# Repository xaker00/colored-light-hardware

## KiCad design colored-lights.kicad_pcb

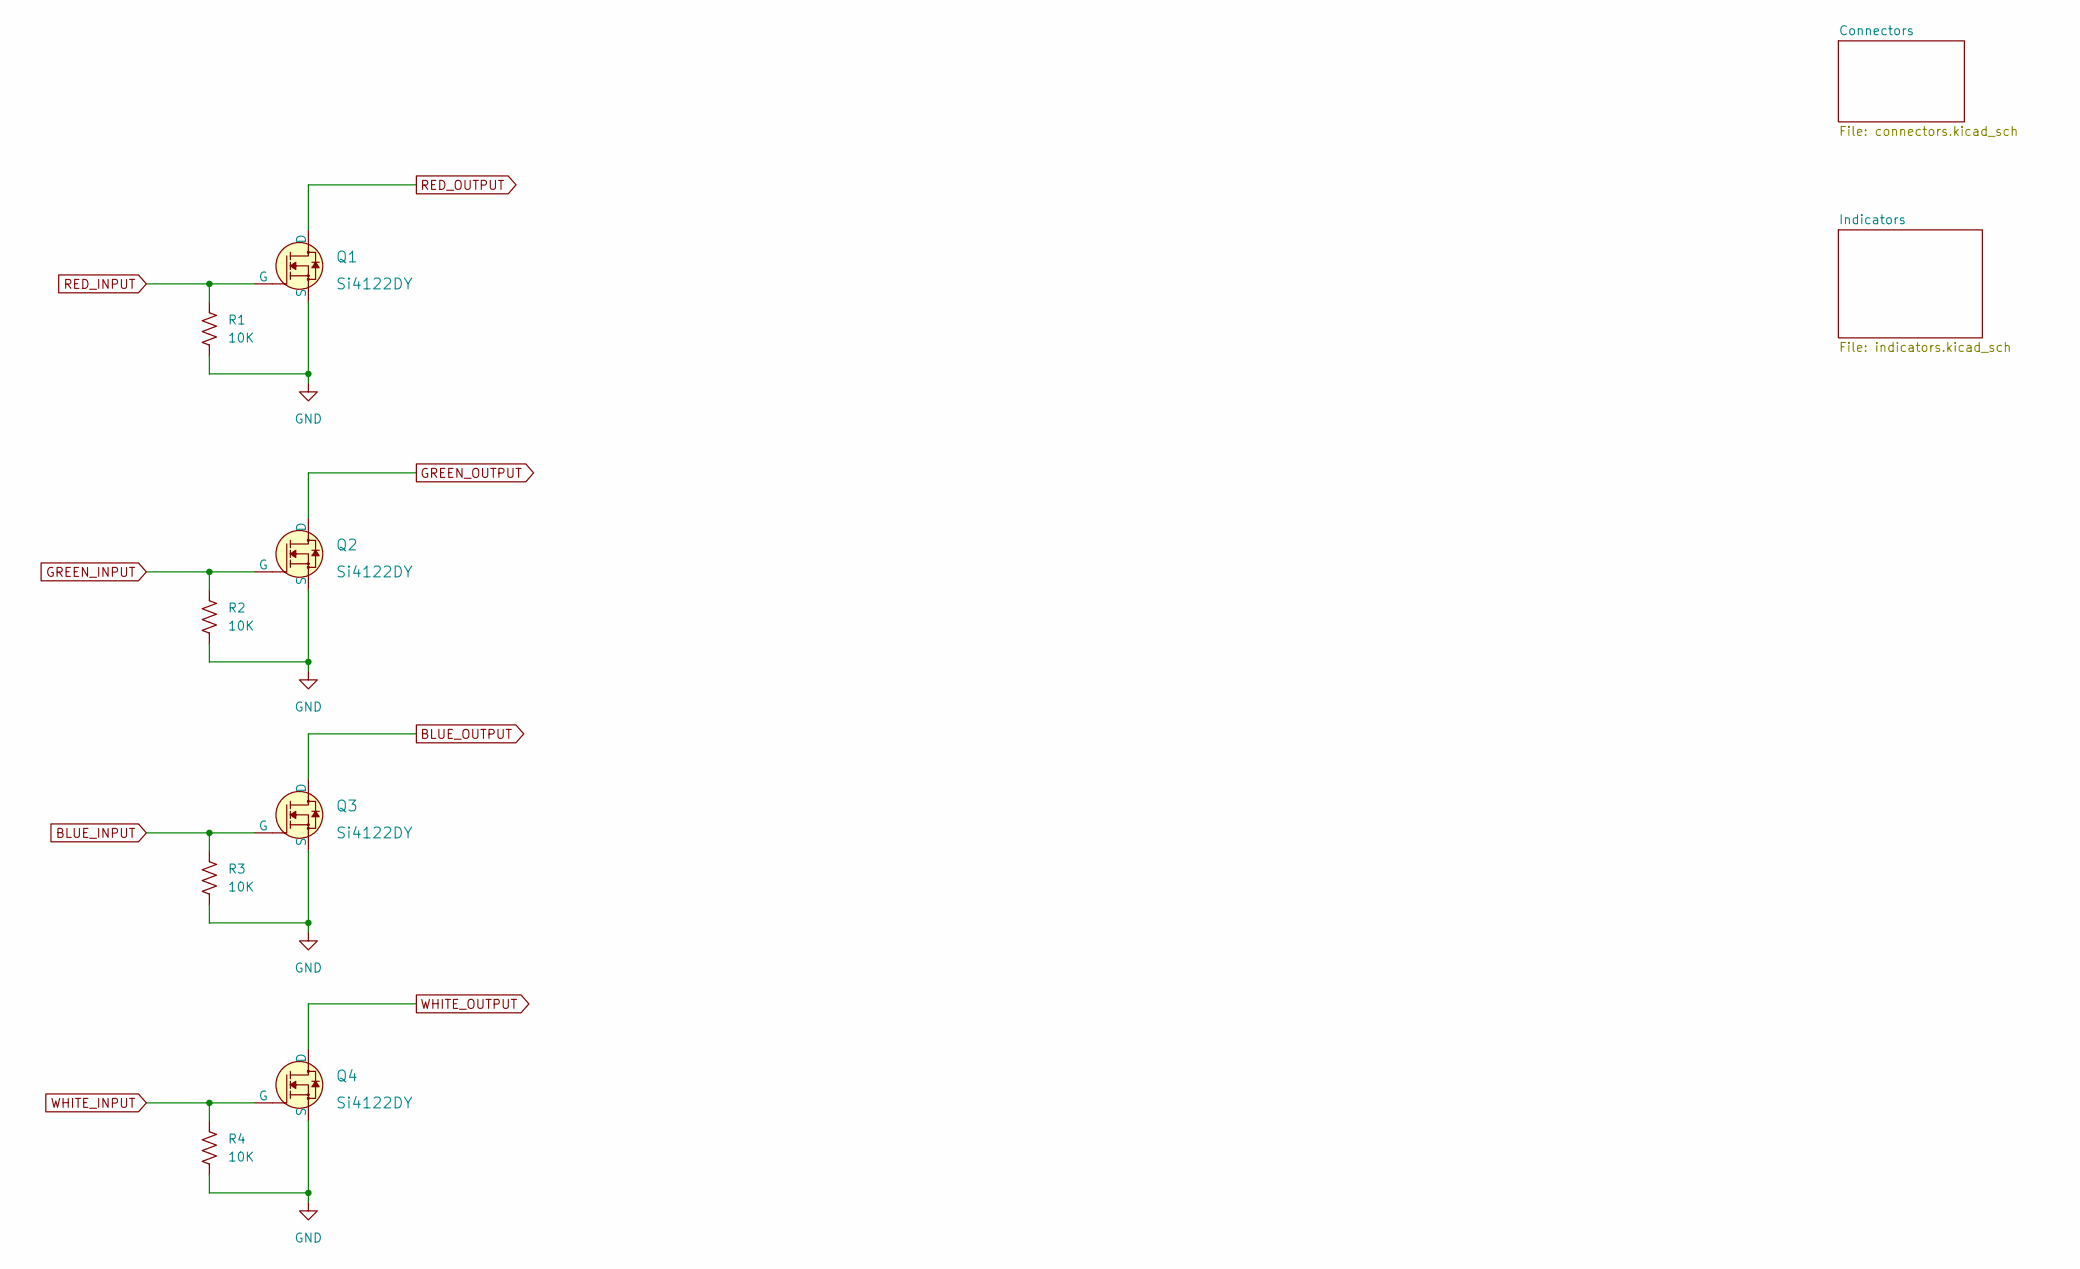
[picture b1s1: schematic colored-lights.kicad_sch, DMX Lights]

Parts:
Q1, Q2, Q3, Q4: Si4122DY; SOIC-8_3.9x4.9mm_P1.27mm transistor
R1, R2, R3, R4: 10K; R_1206_3216Metric

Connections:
BLUE_INPUT: Q3.1 (G), R3.1; also elsewhere on the board
BLUE_OUTPUT: Q3.2 (D); also elsewhere on the board
GND: Q1.3 (S), Q2.3 (S), Q3.3 (S), Q4.3 (S), R1.2, R2.2, R3.2, R4.2; also elsewhere on the board
GREEN_INPUT: Q2.1 (G), R2.1; also elsewhere on the board
GREEN_OUTPUT: Q2.2 (D); also elsewhere on the board
RED_INPUT: Q1.1 (G), R1.1; also elsewhere on the board
RED_OUTPUT: Q1.2 (D); also elsewhere on the board
WHITE_INPUT: Q4.1 (G), R4.1; also elsewhere on the board
WHITE_OUTPUT: Q4.2 (D); also elsewhere on the board

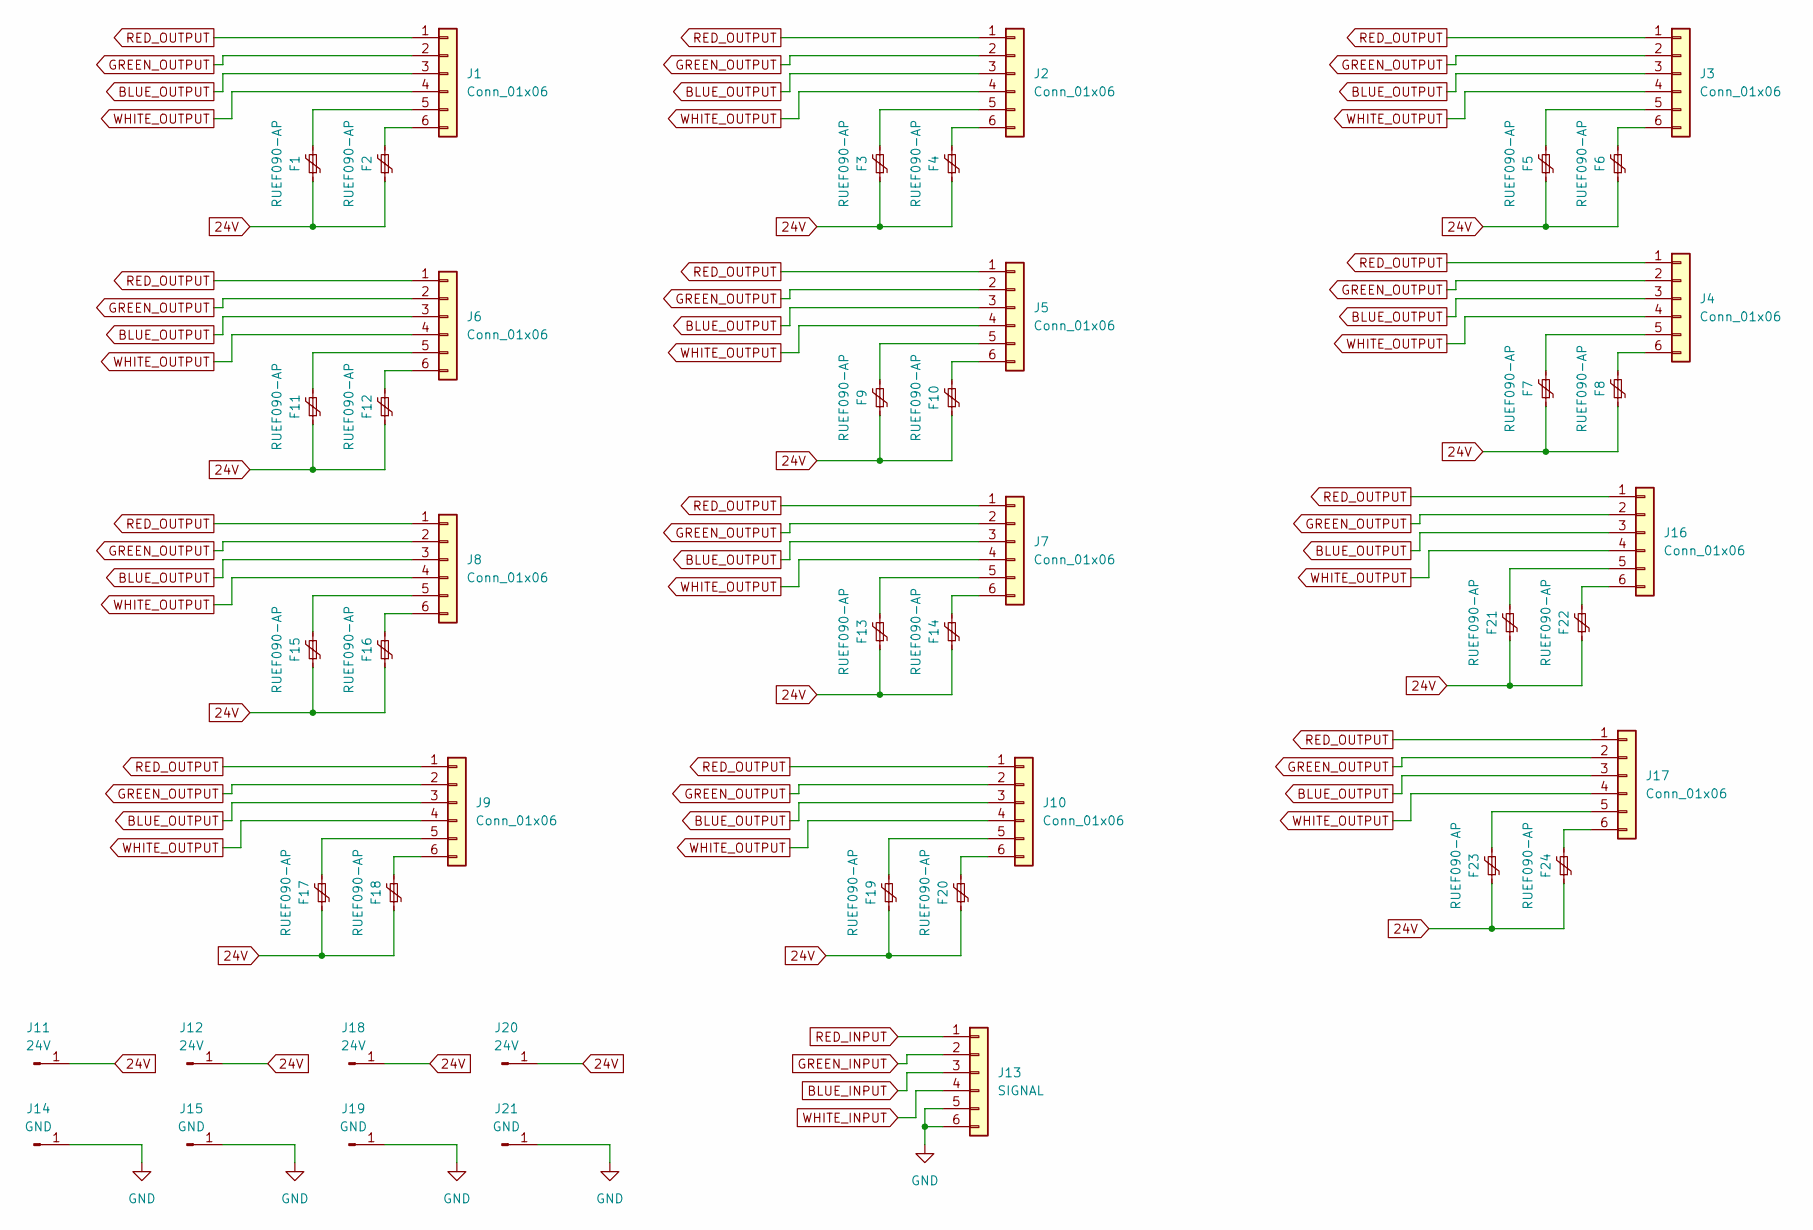
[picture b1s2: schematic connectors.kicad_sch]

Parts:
F1, F2, F3, F4, F5, F6, F7, F8, F9, F10, F11, F12, F13, F14, F15, F16, F17, F18, F19, F20, F21, F22, F23, F24: RUEF090-AP; Fuse_Littelfuse_395Series
J1, J2, J3, J4, J5, J6, J7, J8, J9, J10, J16, J17: Conn_01x06; 1814605
J11, J12, J18, J20: 24V; 1212
J13: SIGNAL; 1814605
J14, J15, J19, J21: GND; 1212

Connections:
24V: F1.1, F2.1, F3.1, F4.1, F5.1, F6.1, F7.1, F8.1, F9.1, F10.1, F11.1, F12.1, F13.1, F14.1, F15.1, F16.1, F17.1, F18.1, F19.1, F20.1, F21.1, F22.1, F23.1, F24.1, J11.1, J12.1, J18.1, J20.1; also elsewhere on the board
BLUE_INPUT: J13.3; also elsewhere on the board
BLUE_OUTPUT: J1.3, J2.3, J3.3, J4.3, J5.3, J6.3, J7.3, J8.3, J9.3, J10.3, J16.3, J17.3; also elsewhere on the board
GND: J13.5, J13.6, J14.1, J15.1, J19.1, J21.1; also elsewhere on the board
GREEN_INPUT: J13.2; also elsewhere on the board
GREEN_OUTPUT: J1.2, J2.2, J3.2, J4.2, J5.2, J6.2, J7.2, J8.2, J9.2, J10.2, J16.2, J17.2; also elsewhere on the board
unnamed: F1.2, J1.5
unnamed: F2.2, J1.6
unnamed: F3.2, J2.5
unnamed: F4.2, J2.6
unnamed: F5.2, J3.5
unnamed: F6.2, J3.6
unnamed: F7.2, J4.5
unnamed: F8.2, J4.6
unnamed: F9.2, J5.5
unnamed: F10.2, J5.6
unnamed: F11.2, J6.5
unnamed: F12.2, J6.6
unnamed: F13.2, J7.5
unnamed: F14.2, J7.6
unnamed: F15.2, J8.5
unnamed: F16.2, J8.6
unnamed: F17.2, J9.5
unnamed: F18.2, J9.6
unnamed: F19.2, J10.5
unnamed: F20.2, J10.6
unnamed: F21.2, J16.5
unnamed: F22.2, J16.6
unnamed: F23.2, J17.5
unnamed: F24.2, J17.6
RED_INPUT: J13.1; also elsewhere on the board
RED_OUTPUT: J1.1, J2.1, J3.1, J4.1, J5.1, J6.1, J7.1, J8.1, J9.1, J10.1, J16.1, J17.1; also elsewhere on the board
WHITE_INPUT: J13.4; also elsewhere on the board
WHITE_OUTPUT: J1.4, J2.4, J3.4, J4.4, J5.4, J6.4, J7.4, J8.4, J9.4, J10.4, J16.4, J17.4; also elsewhere on the board

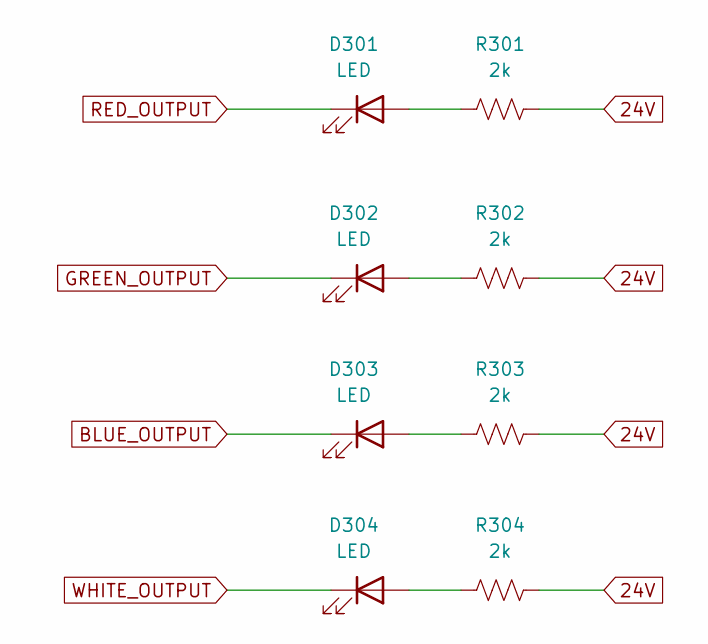
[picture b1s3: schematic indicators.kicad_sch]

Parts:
D301, D302, D303, D304: LED; LED_1206_3216Metric
R301, R302, R303, R304: 2k; R_2010_5025Metric

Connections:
24V: R301.2, R302.2, R303.2, R304.2; also elsewhere on the board
BLUE_OUTPUT: D303.1 (K); also elsewhere on the board
GREEN_OUTPUT: D302.1 (K); also elsewhere on the board
unnamed: D301.2 (A), R301.1
unnamed: D302.2 (A), R302.1
unnamed: D303.2 (A), R303.1
unnamed: D304.2 (A), R304.1
RED_OUTPUT: D301.1 (K); also elsewhere on the board
WHITE_OUTPUT: D304.1 (K); also elsewhere on the board

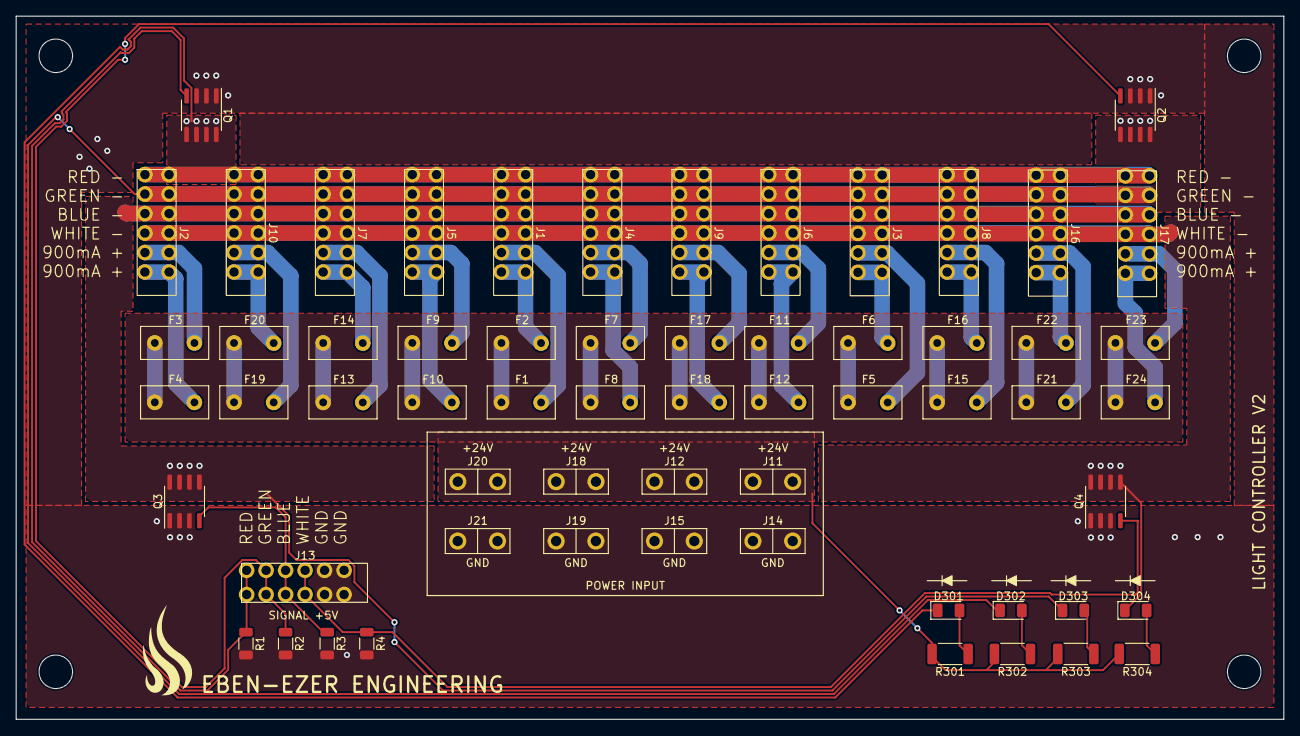
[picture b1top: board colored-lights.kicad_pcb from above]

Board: 2 copper layers, 162.6 x 90.2 mm, 65 parts (0 on the bottom side), 38 nets.

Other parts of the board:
 : MountingHole_4.3mm_M4
 #2,  #3,  #4: MountingHole_4.3mm_M4

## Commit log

2022-03-06 changed to SO-8 MOSFETs
2022-04-07 finish p1 board layout
2022-04-21 Adjusted indicator LEDs * Increased value to decrease brightness and power usage * Increased size to handle heat and make assembly easier
2022-04-21 Silkscreen updates & improvements
2022-04-21 corrected typo
